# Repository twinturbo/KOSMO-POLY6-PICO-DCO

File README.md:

# KOSMO-POLY6-PICO-DCO 
This repository contains KICAD Schematics, PCB and front panel to build a 6 voice Raspberry Pi Pico Based Digitaly Controlled Oscilator for the "Polykit" Inspired 6 Channel Synth in Kosmo Format [Look Mum No Computer LMNK]. The credit for the desigin and code goes to the original Project by Jan Knipper AKA PolyKit [PolyKit DCO](https://github.com/polykit/pico-dco)

This project requires a Raspbery Pi Pico MCU.

Parts of the following information are by Jan AKA Polykit from the original repository

## About KOSMO-POLY6
The [POLY6](https://github.com/twinturbo/KOSMO-POLY6) GIT contains the details of the porject as a whole, this is one module.

Other modules in the line up are

- KOSMO-POLY6-PICO-DCO - Complete [ DCO ](https://github.com/twinturbo/KOSMO-POLY6-PICO-DCO)
- KOSMO-POLY6-DRUID-DCO -(TBD).
- KOSMO-POLY6-JACKS - Complete. [ JACKS ](https://github.com/twinturbo/KOSMO-POLY6-JACKS)
- KOSMO-POLY6-MIX - In design.
- KOSMO-POLY6-ADSR - In Production with JLCPCB.
- KOSMO-POLY6-VCA - In design.
- KOSMO-POLY6-CONTROLS - (TBD).
- KOSMO-POLY6 Filter - (TBD).
- KOSMO-POLY6-PG Programmer - (TBD)
- KOSMO-POLY6-MetricST-Front-Panel - (TBD)

# KOSMO-POLY6-PICO-DCO Details

The DCO utilises a Raspbery PI Pico using it's PWM Pins to generate a highly accurate frequency and gate signals. It can be controlled by USB MIDI or Standard 5 Pin serial MIDI. The analog oscillator part is based on the Juno 106 and generates sawtooth and square wave signal with a 10Vpp amplitude. Amplitude compensation is done by a smoothed PWM signal coming from the Pico.

## Key features

- Digitally controlled analog oscillator using a Raspberry Pi Pico
- Up to six voices
- Voice stacking             ------ [ requires sub control board ] See > Not Done
- Detuning of voices         ------ [ requires sub control board ] See > Not Done
- Frequency modulation (FM)  ------ [ requires sub control board ] See > Not Done
- Separate gate signal 
- DIN MIDI serial input
- USB MIDI input
- MIDI pitch bend (Via MIDI CC )
- Portamento with adjustable speed ( Via MIDI CC )
- Voltage and Midi telltale LED's
- Power pass through for sub modules.

## How does Jan's Sound & Look
These are examples of how the originator Jan Knipper's sound.
This is how it sounds: 

- [Ramp sample](https://soundcloud.com/polykit/pico-dco-ramp) 
- [Pulse sample](https://soundcloud.com/polykit/pico-dco-pulse) 
- [Polyphonic sample](https://soundcloud.com/polykit/pico-dco-polyphonic)

And in use with Jan 
- Youtube[Tube](https://www.youtube.com/watch?v=vj-DSh6yfM0)
- Youtube[Tube](https://www.youtube.com/watch?v=go1mErOdtsU)

## Schematics and PCB
Schematics in Kicad format can be found for the PCB and Front Panel

[MAIN-BOARD](HARDWARE/MAIN-BOARD) 
[MAIN-BOARD](HARDWARE/FRONT_PANEL) 

Gerber files for the PCB and front panel can be found [here](HARDWARE\PCB-PRINTS).

## Pictures 

## Installation on the paspbery Pi Pico (simple)
The software has been written in C++ and compiled into a uf2 format for the PICO, 

Two files are provided in the software/build folder along with the source code in the software folder

### Disabled Options
pico-dco-optdisab.uf2 is built with the options for FM, STACK and Detune disabled. This is ideal if you don't have these inputs connected.

//#define USE_ADC_STACK_VOICES // gpio 28 (adc 2)

//#define USE_ADC_DETUNE       // gpio 27 (adc 1)

//#define USE_ADC_FM           // gpio 26 (adc 0)

### Enabled Options
pico-dco-options.uf2 has the above options enabled.

#define USE_ADC_STACK_VOICES // gpio 28 (adc 2)

#define USE_ADC_DETUNE       // gpio 27 (adc 1)

#define USE_ADC_FM           // gpio 26 (adc 0)

### Writing to the MCU.

You will need the file on your computer, and whilst plugging in the PICO to USB hold the `BOOTSEL` button. 

The computer should recognise it as a Mass storage device, Copy desired UF2 file  onto the USB mass storage device. The PICO will reboot into operating mode. Note that if you run the bootsel again the file will not be there, it's not possible to confirm the upload.

## Usage

After building the module and installing the Pico should register as USB MIDI device. Alternatively serial MIDI input is available. The DCO listens to note on/note off messages on MIDI channel 1. Pitch bend is also supported. Portamento can be enabled by MIDI CC message #65, portamento time can be adjusted by CC message #5.

MIDI Device in Cakewalk

The 6 notes play all the time, hence there is a need for an ADSR and VCA to close the note off. Each new note played replaces the oldest in the group in a cyclic fashion.

## Detuning, stacking and FM

The built-in analog-to-digital converter can be used to modulate these parameters. You can add an external control voltage (0-3.3V) to that input pins. These features can be disabled by commenting (`//`) the following lines:

As mentioned above, these are not implemented in hardware on this module but a seperate control module needs to be built. 

#define USE_ADC_STACK_VOICES // gpio 28 (adc 2)

#define USE_ADC_DETUNE       // gpio 27 (adc 1)

#define USE_ADC_FM           // gpio 26 (adc 0)

Hardware wise the FM needs to be biased at 1.675v for zero input , the notes on this can be found in the source code **loop void adc_task()**

## Quirks

Initialy the voices will be floating on startup, which if directly outputed ( not through an ADSR/VCA ) may present as noise, as each of the voices is initialised by a key press the noise will go away. 

## Changes 
TwinTurbo 12/3/23 - 
Ref: > https://lookmumnocomputer.discourse.group/t/raspberry-pi-pico-dco/3421/90
updated source code from 0x90 to 0x9F

# References
The Original 
https://github.com/polykit/pico-dco

https://blog.thea.codes/the-design-of-the-juno-dco/

https://electricdruid.net/roland-juno-dcos/

https://www.youtube.com/watch?v=yYnQYF_Xa8g

https://github.com/raspberrypi/pico-examples/tree/master/pio/pwm

https://github.com/raspberrypi/pico-examples/tree/master/pio/pio_blink

https://github.com/raspberrypi/pico-examples/tree/master/pwm/hello_pwm

https://qiita.com/jamjam/items/f2fdd5c072ff348fd809

https://github.com/infovore/pico-example-midi

https://learn.sparkfun.com/tutorials/midi-tutorial/all

http://www.music-software-development.com/midi-tutorial.html

http://midi.teragonaudio.com/tech/midispec/run.htm

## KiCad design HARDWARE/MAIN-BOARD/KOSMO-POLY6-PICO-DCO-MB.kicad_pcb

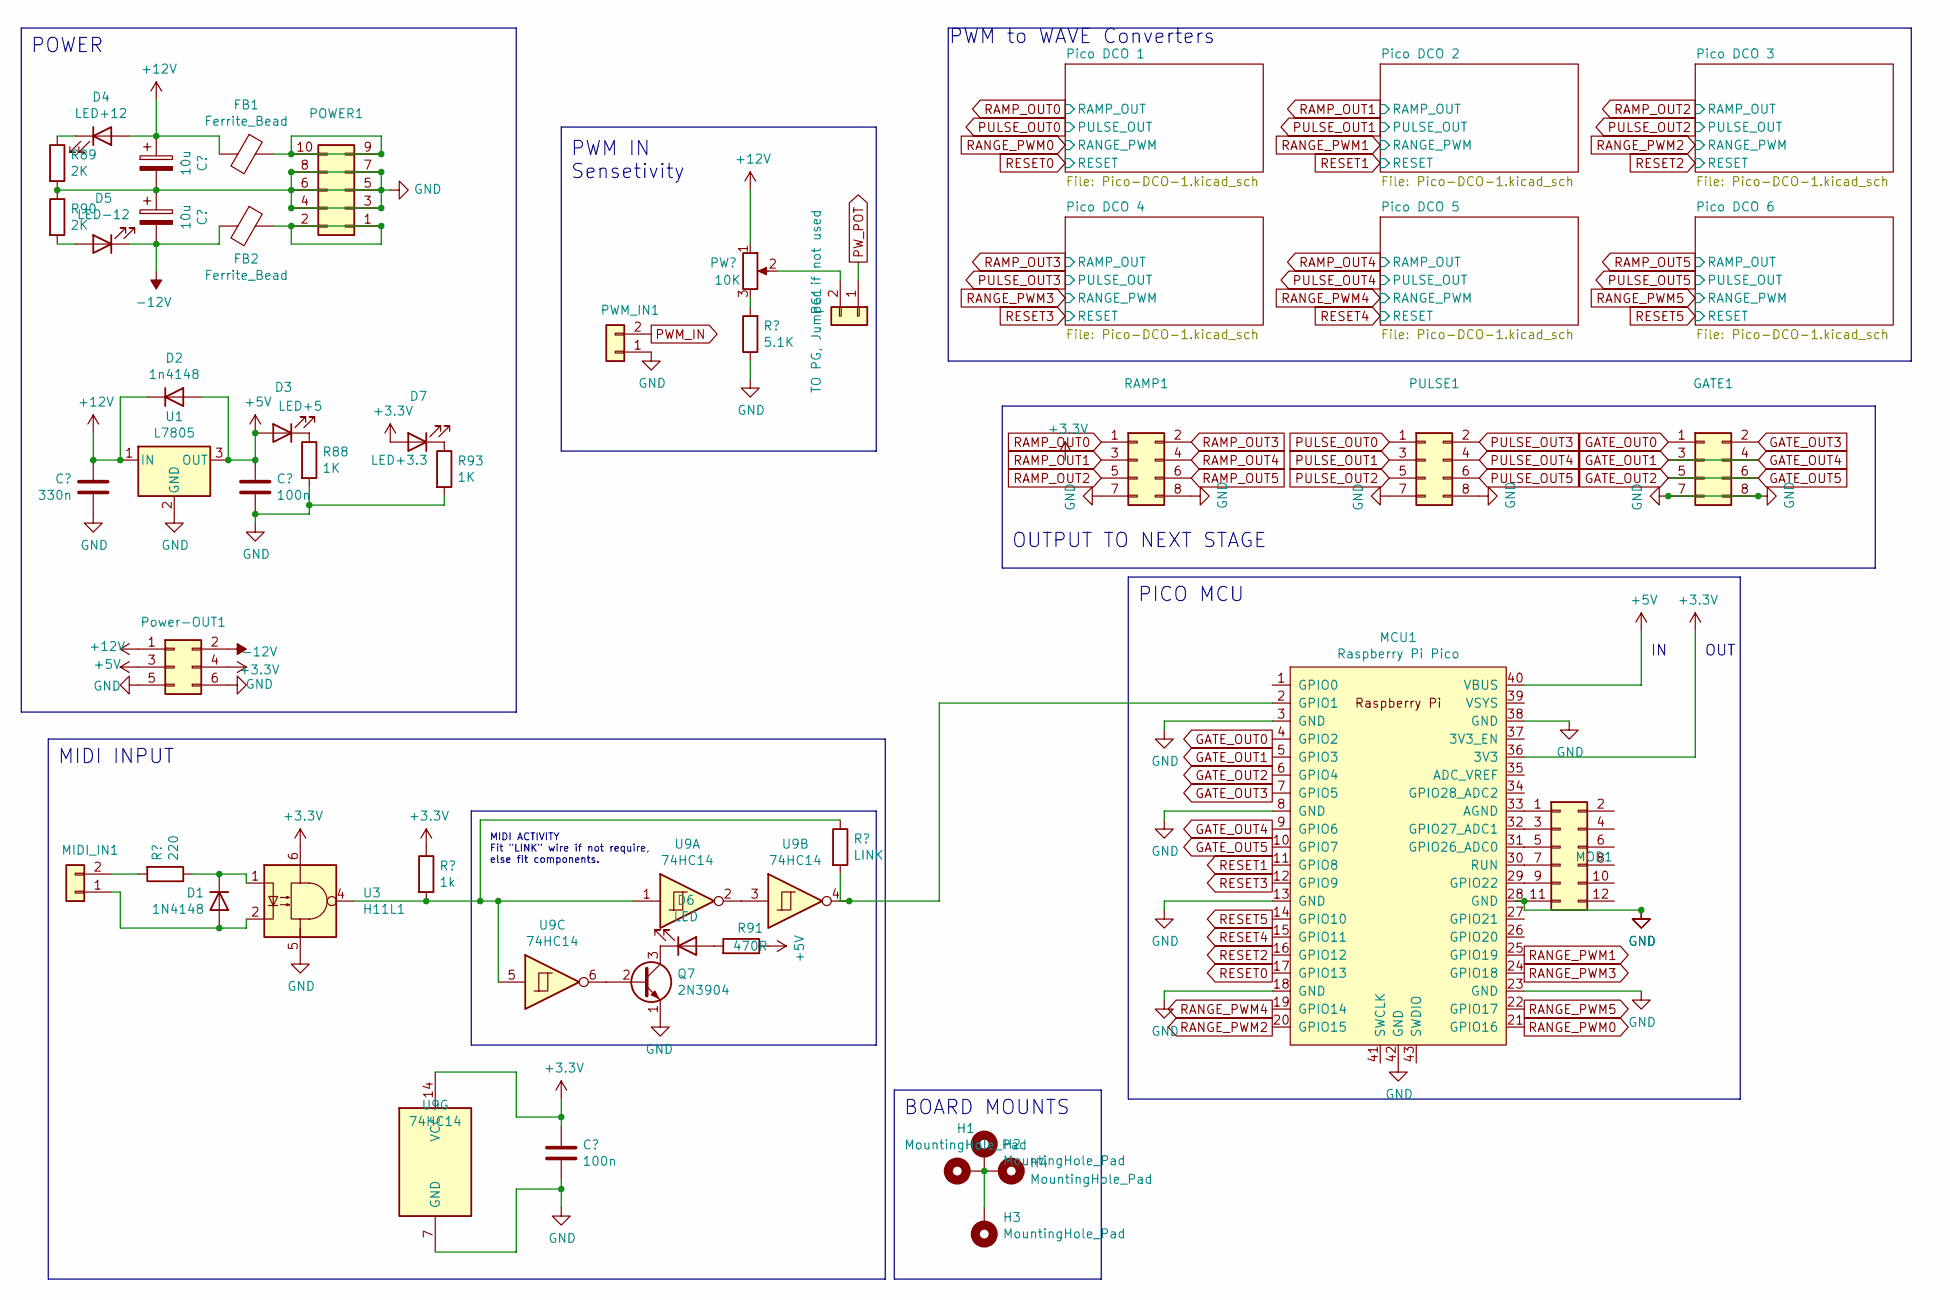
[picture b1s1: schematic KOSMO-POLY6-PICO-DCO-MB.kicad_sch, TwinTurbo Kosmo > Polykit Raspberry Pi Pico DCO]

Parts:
C6: 330n; C_Rect_L7.2mm_W4.5mm_P5.00mm_FKS2_FKP2_MKS2_MKP2
C7, C10: 100n; C_Rect_L7.2mm_W4.5mm_P5.00mm_FKS2_FKP2_MKS2_MKP2
C8, C9: 10u; CP_Radial_D5.0mm_P2.00mm
D1: 1N4148; D_DO-35_SOD27_P7.62mm_Horizontal
D2: 1n4148; D_DO-35_SOD27_P7.62mm_Horizontal
D3: LED+5; LED_D5.0mm
D4: LED+12; LED_D5.0mm
D5: LED-12; LED_D5.0mm
D6: LED; LED_D5.0mm
D7: LED+3.3; LED_D5.0mm
FB1, FB2: Ferrite_Bead; R_Axial_DIN0207_L6.3mm_D2.5mm_P10.16mm_Horizontal
GATE1: Conn_02x04_Odd_Even; IDC-Header_2x04_P2.54mm_Vertical
H1, H2, H3, H4: MountingHole_Pad; MountingHole_3.2mm_M3_DIN965_Pad
MCU1: Raspberry Pi Pico; RPi_Pico_SMD_TH
MIDI_IN1: Conn_01x02; Molex_KK-254_AE-6410-02A_1x02_P2.54mm_Vertical
MOD1: Conn_01x10; IDC-Header_2x06_P2.54mm_Vertical
PG1: TO PG, Jumper if not used; Molex_KK-254_AE-6410-02A_1x02_P2.54mm_Vertical
POWER1: Conn_02x05_Odd_Even; IDC-Header_2x05_P2.54mm_Vertical
PULSE1: Conn_02x04_Odd_Even; IDC-Header_2x04_P2.54mm_Vertical
PWM_IN1: Conn_01x02; Molex_KK-254_AE-6410-02A_1x02_P2.54mm_Vertical
PW_POT1: 10K; Potentiometer_Alps_RK09K_Single_Vertical
Power-OUT1: Conn_02x04_Odd_Even; IDC-Header_2x03_P2.54mm_Vertical
Q7: 2N3904; TO-92_Inline
R4: 5.1K; R_Axial_DIN0207_L6.3mm_D2.5mm_P2.54mm_Vertical
R16: 220; R_Axial_DIN0207_L6.3mm_D2.5mm_P2.54mm_Vertical
R17: 1k; R_Axial_DIN0207_L6.3mm_D2.5mm_P2.54mm_Vertical
R88, R93: 1K; R_Axial_DIN0207_L6.3mm_D2.5mm_P2.54mm_Vertical
R89, R90: 2K; R_Axial_DIN0207_L6.3mm_D2.5mm_P2.54mm_Vertical
R91: 470R; R_Axial_DIN0207_L6.3mm_D2.5mm_P2.54mm_Vertical
R92: LINK; R_Axial_DIN0207_L6.3mm_D2.5mm_P2.54mm_Vertical
RAMP1: Conn_02x04_Odd_Even; IDC-Header_2x04_P2.54mm_Vertical
U1: L7805; TO-220-3_Vertical
U3: H11L1; DIP-6_W7.62mm_Socket_LongPads
U9: 74HC14; DIP-14_W7.62mm

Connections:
+3V3: C10.1, D7.2 (A), MCU1.36 (3V3), Power-OUT1.4, R17.1, U3.6, U9.14 (VCC)
+5V: C7.1, D2.2 (A), D3.2 (A), MCU1.40 (VBUS), Power-OUT1.3, R91.1, U1.3 (OUT)
+12V: C6.2, C8.1, D2.1 (K), D4.2 (A), FB1.2, PW_POT1.1, Power-OUT1.1, U1.1 (IN); also elsewhere on the board
-12V: C9.2, D5.1 (K), FB2.2, Power-OUT1.2; also elsewhere on the board
GATE_OUT0: GATE1.1, MCU1.4 (GPIO2)
GATE_OUT1: GATE1.3, GATE1.4, MCU1.5 (GPIO3), MCU1.9 (GPIO6)
GATE_OUT2: GATE1.5, GATE1.6, MCU1.6 (GPIO4), MCU1.10 (GPIO7)
GATE_OUT3: GATE1.2, MCU1.7 (GPIO5)
GND: C6.1, C7.2, C8.2, C9.1, C10.2, GATE1.7, GATE1.8, MCU1.3 (GND), MCU1.8 (GND), MCU1.13 (GND), MCU1.18 (GND), MCU1.23 (GND), MCU1.28 (GND), MCU1.38 (GND), MCU1.42 (GND), MOD1.11, POWER1.3, POWER1.4, POWER1.5, POWER1.6, POWER1.7, POWER1.8, PULSE1.7, PULSE1.8, PWM_IN1.1, Power-OUT1.5, Power-OUT1.6, Q7.1 (E), R4.1, R88.2, R89.2, R90.1, R93.2, RAMP1.7, RAMP1.8, U1.2 (GND), U3.5, U9.7 (GND); also elsewhere on the board
unnamed: D1.1 (K), R16.1, U3.1
unnamed: D1.2 (A), MIDI_IN1.1, U3.2
unnamed: D3.1 (K), R88.1
unnamed: D4.1 (K), R89.1
unnamed: D5.2 (A), R90.2
unnamed: D6.1 (K), Q7.3 (C)
unnamed: D6.2 (A), R91.2
unnamed: D7.1 (K), R93.1
unnamed: FB1.1, POWER1.9, POWER1.10
unnamed: FB2.1, POWER1.1, POWER1.2
unnamed: H1.1, H2.1, H3.1, H4.1
unnamed: MCU1.2 (GPIO1), R92.2, U9.4
unnamed: MCU1.29 (GPIO22), MOD1.9
unnamed: MCU1.30 (RUN), MOD1.7
unnamed: MCU1.31 (GPIO26_ADC0), MOD1.5
unnamed: MCU1.32 (GPIO27_ADC1), MOD1.3
unnamed: MCU1.33 (AGND), MOD1.1
unnamed: MIDI_IN1.2, R16.2
unnamed: PG1.2, PW_POT1.2
unnamed: PW_POT1.3, R4.2
unnamed: Q7.2 (B), U9.6
unnamed: R17.2, R92.1, U3.4, U9.1, U9.5
unnamed: U9.2, U9.3
PULSE_OUT0: PULSE1.1; also elsewhere on the board
PULSE_OUT1: PULSE1.3; also elsewhere on the board
PULSE_OUT2: PULSE1.5; also elsewhere on the board
PULSE_OUT3: PULSE1.2; also elsewhere on the board
PULSE_OUT4: PULSE1.4; also elsewhere on the board
PULSE_OUT5: PULSE1.6; also elsewhere on the board
PWM_IN: PWM_IN1.2; also elsewhere on the board
PW_POT: PG1.1; also elsewhere on the board
RAMP_OUT0: RAMP1.1; also elsewhere on the board
RAMP_OUT1: RAMP1.3; also elsewhere on the board
RAMP_OUT2: RAMP1.5; also elsewhere on the board
RAMP_OUT3: RAMP1.2; also elsewhere on the board
RAMP_OUT4: RAMP1.4; also elsewhere on the board
RAMP_OUT5: RAMP1.6; also elsewhere on the board
RANGE_PWM0: MCU1.21 (GPIO16); also elsewhere on the board
RANGE_PWM1: MCU1.25 (GPIO19); also elsewhere on the board
RANGE_PWM2: MCU1.20 (GPIO15); also elsewhere on the board
RANGE_PWM3: MCU1.24 (GPIO18); also elsewhere on the board
RANGE_PWM4: MCU1.19 (GPIO14); also elsewhere on the board
RANGE_PWM5: MCU1.22 (GPIO17); also elsewhere on the board
RESET0: MCU1.17 (GPIO13); also elsewhere on the board
RESET1: MCU1.11 (GPIO8); also elsewhere on the board
RESET2: MCU1.16 (GPIO12); also elsewhere on the board
RESET3: MCU1.12 (GPIO9); also elsewhere on the board
RESET4: MCU1.15 (GPIO11); also elsewhere on the board
RESET5: MCU1.14 (GPIO10); also elsewhere on the board

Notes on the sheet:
POWER
PICO MCU
OUT
PWM to WAVE Converters
MIDI ACTIVITY Fit "LINK" wire if not require, else fit components.
BOARD MOUNTS
PWM IN Sensetivity
MIDI INPUT
OUTPUT TO NEXT STAGE

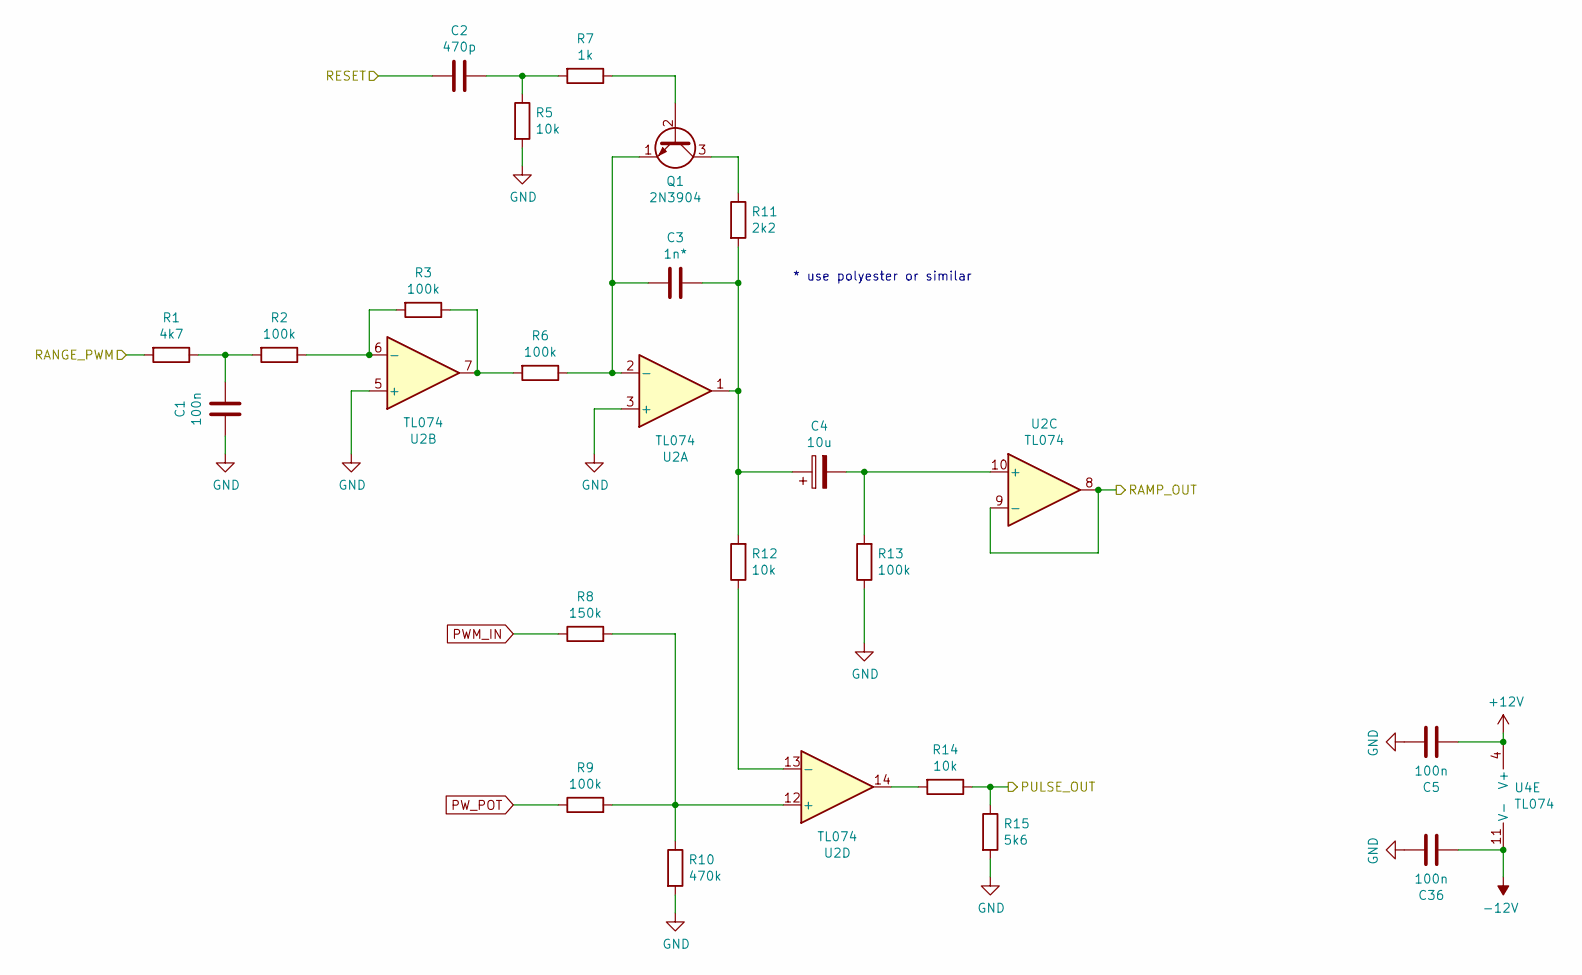
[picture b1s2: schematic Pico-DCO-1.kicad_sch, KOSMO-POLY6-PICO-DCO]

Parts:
C1, C5, C36: 100n; C_Rect_L7.2mm_W4.5mm_P5.00mm_FKS2_FKP2_MKS2_MKP2
C2: 470p; C_Rect_L7.2mm_W4.5mm_P5.00mm_FKS2_FKP2_MKS2_MKP2
C3: 1n*; C_Rect_L7.2mm_W4.5mm_P5.00mm_FKS2_FKP2_MKS2_MKP2
C4: 10u; CP_Radial_D5.0mm_P2.00mm
Q1: 2N3904; TO-92_Wide
R1: 4k7; R_Axial_DIN0207_L6.3mm_D2.5mm_P2.54mm_Vertical
R2, R3, R6, R9, R13: 100k; R_Axial_DIN0207_L6.3mm_D2.5mm_P2.54mm_Vertical
R5, R12, R14: 10k; R_Axial_DIN0207_L6.3mm_D2.5mm_P2.54mm_Vertical
R7: 1k; R_Axial_DIN0207_L6.3mm_D2.5mm_P2.54mm_Vertical
R8: 150k; R_Axial_DIN0207_L6.3mm_D2.5mm_P2.54mm_Vertical
R10: 470k; R_Axial_DIN0207_L6.3mm_D2.5mm_P2.54mm_Vertical
R11: 2k2; R_Axial_DIN0207_L6.3mm_D2.5mm_P2.54mm_Vertical
R15: 5k6; R_Axial_DIN0207_L6.3mm_D2.5mm_P2.54mm_Vertical
U2, U4: TL074; DIP-14_W7.62mm_Socket_LongPads

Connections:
+12V: C5.2, U2.4 (V+), U4.4 (V+); also elsewhere on the board
-12V: C36.2, U2.11 (V-), U4.11 (V-); also elsewhere on the board
GND: C1.2, C5.1, C36.1, R5.2, R10.2, R13.1, R15.2, U2.3 (+), U2.5 (+), U4.3 (+), U4.5 (+); also elsewhere on the board
unnamed: C1.1, R1.1, R2.2
unnamed: C2.1, R5.1, R7.2
unnamed: C3.1, C4.1, R11.2, R12.2, U2.1
unnamed: C3.2, Q1.1 (E), R6.1, U2.2 (-)
unnamed: C4.2, R13.2, U2.10 (+)
unnamed 16: U4.1; also elsewhere on the board
unnamed 17: U4.2 (-); also elsewhere on the board
unnamed 18: U4.10 (+); also elsewhere on the board
unnamed: Q1.2 (B), R7.1
unnamed: Q1.3 (C), R11.1
unnamed: R2.1, R3.2, U2.6 (-)
unnamed: R3.1, R6.2, U2.7
unnamed: R8.2, R9.2, R10.1, U2.12 (+)
unnamed: R12.1, U2.13 (-)
unnamed: R14.2, U2.14
unnamed 93: U4.6 (-); also elsewhere on the board
unnamed 94: U4.7; also elsewhere on the board
unnamed 95: U4.12 (+); also elsewhere on the board
unnamed 96: U4.13 (-); also elsewhere on the board
unnamed 97: U4.14; also elsewhere on the board
PULSE_OUT0: R14.1, R15.1; also elsewhere on the board
PWM_IN: R8.1; also elsewhere on the board
PW_POT: R9.1; also elsewhere on the board
RAMP_OUT0: U2.8, U2.9 (-); also elsewhere on the board
RAMP_OUT1: U4.8, U4.9 (-); also elsewhere on the board
RANGE_PWM0: R1.2; also elsewhere on the board
RESET0: C2.2; also elsewhere on the board

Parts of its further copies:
C11, C15, C16, C20, C21, C25, C26, C30, C31, C35, C37, C38, C39, C40, C41: 100n; C_Rect_L7.2mm_W4.5mm_P5.00mm_FKS2_FKP2_MKS2_MKP2
C12, C17, C22, C27, C32: 470p; C_Rect_L7.2mm_W4.5mm_P5.00mm_FKS2_FKP2_MKS2_MKP2
C13, C18, C23, C28, C33: 1n*; C_Rect_L7.2mm_W4.5mm_P5.00mm_FKS2_FKP2_MKS2_MKP2
C14, C19, C24, C29, C34: 10u; CP_Radial_D5.0mm_P2.00mm
Q2, Q3, Q4, Q5, Q6: 2N3904; TO-92_Wide
R18, R32, R46, R60, R74: 4k7; R_Axial_DIN0207_L6.3mm_D2.5mm_P2.54mm_Vertical
R19, R20, R22, R25, R29, R33, R34, R36, R39, R43, R47, R48, R50, R53, R57, R61, R62, R64, R67, R71, R75, R76, R78, R81, R85: 100k; R_Axial_DIN0207_L6.3mm_D2.5mm_P2.54mm_Vertical
R21, R28, R30, R35, R42, R44, R49, R56, R58, R63, R70, R72, R77, R84, R86: 10k; R_Axial_DIN0207_L6.3mm_D2.5mm_P2.54mm_Vertical
R23, R37, R51, R65, R79: 1k; R_Axial_DIN0207_L6.3mm_D2.5mm_P2.54mm_Vertical
R24, R38, R52, R66, R80: 150k; R_Axial_DIN0207_L6.3mm_D2.5mm_P2.54mm_Vertical
R26, R40, R54, R68, R82: 470k; R_Axial_DIN0207_L6.3mm_D2.5mm_P2.54mm_Vertical
R27, R41, R55, R69, R83: 2k2; R_Axial_DIN0207_L6.3mm_D2.5mm_P2.54mm_Vertical
R31, R45, R59, R73, R87: 5k6; R_Axial_DIN0207_L6.3mm_D2.5mm_P2.54mm_Vertical
U5, U6, U7, U8: TL074; DIP-14_W7.62mm_Socket_LongPads

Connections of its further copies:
+12V: C15.2, C20.2, C25.2, C30.2, C35.2, U5.4 (V+), U6.4 (V+), U7.4 (V+), U8.4 (V+); also elsewhere on the board
-12V: C37.2, C38.2, C39.2, C40.2, C41.2, U5.11 (V-), U6.11 (V-), U7.11 (V-), U8.11 (V-); also elsewhere on the board
GND: C11.2, C15.1, C16.2, C20.1, C21.2, C25.1, C26.2, C30.1, C31.2, C35.1, C37.1, C38.1, C39.1, C40.1, C41.1, R21.2, R26.2, R29.1, R31.2, R35.2, R40.2, R43.1, R45.2, R49.2, R54.2, R57.1, R59.2, R63.2, R68.2, R71.1, R73.2, R77.2, R82.2, R85.1, R87.2, U5.3 (+), U5.5 (+), U6.3 (+), U6.5 (+), U7.3 (+), U7.5 (+), U8.3 (+), U8.5 (+); also elsewhere on the board
unnamed: C11.1, R18.1, R19.2
unnamed: C12.1, R21.1, R23.2
unnamed 16: C13.1, C14.1, R27.2, R28.2; also elsewhere on the board
unnamed 17: C13.2, Q2.1 (E), R22.1; also elsewhere on the board
unnamed 18: C14.2, R29.2; also elsewhere on the board
unnamed: C16.1, R32.1, R33.2
unnamed: C17.1, R35.1, R37.2
unnamed: C18.1, C19.1, R41.2, R42.2, U5.1
unnamed: C18.2, Q3.1 (E), R36.1, U5.2 (-)
unnamed: C19.2, R43.2, U5.10 (+)
unnamed: C21.1, R46.1, R47.2
unnamed: C22.1, R49.1, R51.2
unnamed: C23.1, C24.1, R55.2, R56.2, U6.1
unnamed: C23.2, Q4.1 (E), R50.1, U6.2 (-)
unnamed: C24.2, R57.2, U6.10 (+)
unnamed: C26.1, R60.1, R61.2
unnamed: C27.1, R63.1, R65.2
unnamed: C28.1, C29.1, R69.2, R70.2, U7.1
unnamed: C28.2, Q5.1 (E), R64.1, U7.2 (-)
unnamed: C29.2, R71.2, U7.10 (+)
unnamed: C31.1, R74.1, R75.2
unnamed: C32.1, R77.1, R79.2
unnamed: C33.1, C34.1, R83.2, R84.2, U8.1
unnamed: C33.2, Q6.1 (E), R78.1, U8.2 (-)
unnamed: C34.2, R85.2, U8.10 (+)
unnamed: Q2.2 (B), R23.1
unnamed: Q2.3 (C), R27.1
unnamed: Q3.2 (B), R37.1
unnamed: Q3.3 (C), R41.1
unnamed: Q4.2 (B), R51.1
unnamed: Q4.3 (C), R55.1
unnamed: Q5.2 (B), R65.1
unnamed: Q5.3 (C), R69.1
unnamed: Q6.2 (B), R79.1
unnamed: Q6.3 (C), R83.1
unnamed 93: R19.1, R20.2; also elsewhere on the board
unnamed 94: R20.1, R22.2; also elsewhere on the board
unnamed 95: R24.2, R25.2, R26.1; also elsewhere on the board
unnamed 96: R28.1; also elsewhere on the board
unnamed 97: R30.2; also elsewhere on the board
unnamed: R33.1, R34.2, U5.6 (-)
unnamed: R34.1, R36.2, U5.7
unnamed: R38.2, R39.2, R40.1, U5.12 (+)
unnamed: R42.1, U5.13 (-)
unnamed: R44.2, U5.14
unnamed: R47.1, R48.2, U6.6 (-)
unnamed: R48.1, R50.2, U6.7
unnamed: R52.2, R53.2, R54.1, U6.12 (+)
unnamed: R56.1, U6.13 (-)
unnamed: R58.2, U6.14
unnamed: R61.1, R62.2, U7.6 (-)
unnamed: R62.1, R64.2, U7.7
unnamed: R66.2, R67.2, R68.1, U7.12 (+)
unnamed: R70.1, U7.13 (-)
unnamed: R72.2, U7.14
unnamed: R75.1, R76.2, U8.6 (-)
unnamed: R76.1, R78.2, U8.7
unnamed: R80.2, R81.2, R82.1, U8.12 (+)
unnamed: R84.1, U8.13 (-)
unnamed: R86.2, U8.14
PULSE_OUT1: R30.1, R31.1; also elsewhere on the board
PULSE_OUT2: R44.1, R45.1; also elsewhere on the board
PULSE_OUT3: R58.1, R59.1; also elsewhere on the board
PULSE_OUT4: R72.1, R73.1; also elsewhere on the board
PULSE_OUT5: R86.1, R87.1; also elsewhere on the board
PWM_IN: R24.1, R38.1, R52.1, R66.1, R80.1; also elsewhere on the board
PW_POT: R25.1, R39.1, R53.1, R67.1, R81.1; also elsewhere on the board
RAMP_OUT2: U5.8, U5.9 (-); also elsewhere on the board
RAMP_OUT3: U6.8, U6.9 (-); also elsewhere on the board
RAMP_OUT4: U7.8, U7.9 (-); also elsewhere on the board
RAMP_OUT5: U8.8, U8.9 (-); also elsewhere on the board
RANGE_PWM1: R18.2; also elsewhere on the board
RANGE_PWM2: R32.2; also elsewhere on the board
RANGE_PWM3: R46.2; also elsewhere on the board
RANGE_PWM4: R60.2; also elsewhere on the board
RANGE_PWM5: R74.2; also elsewhere on the board
RESET1: C12.2; also elsewhere on the board
RESET2: C17.2; also elsewhere on the board
RESET3: C22.2; also elsewhere on the board
RESET4: C27.2; also elsewhere on the board
RESET5: C32.2; also elsewhere on the board

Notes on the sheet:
* use polyester or similar

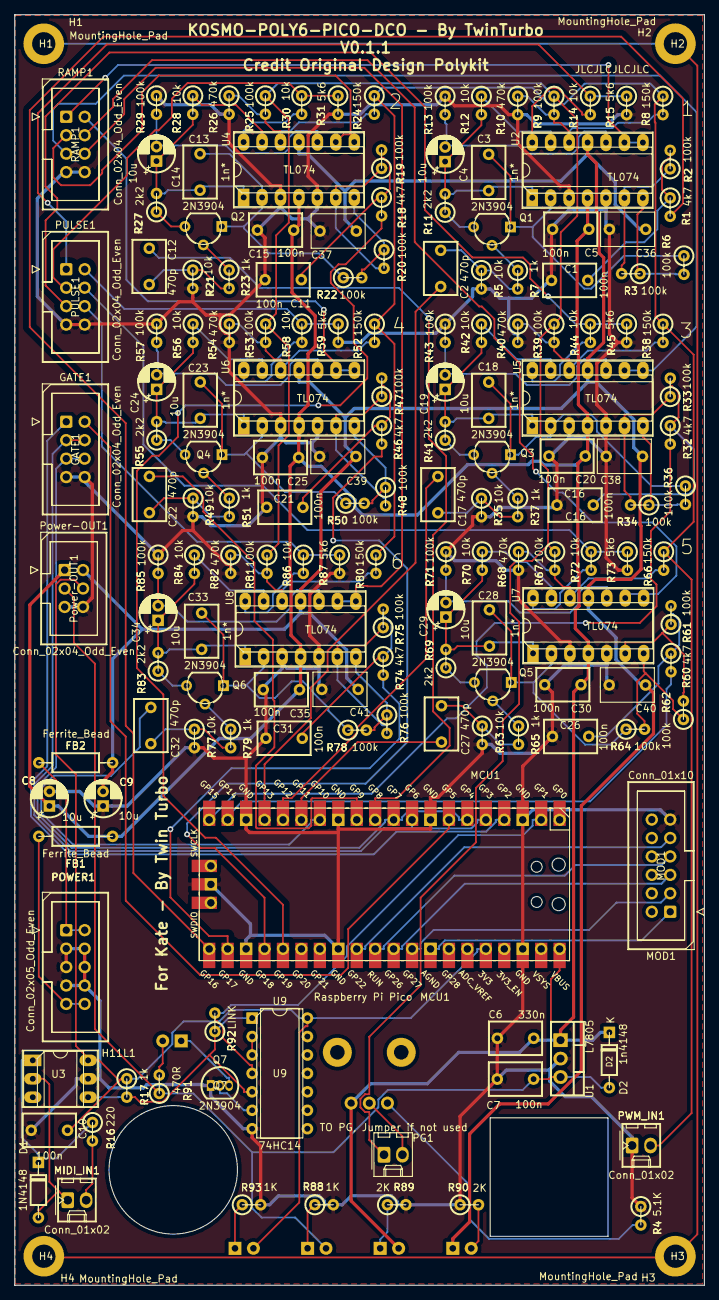
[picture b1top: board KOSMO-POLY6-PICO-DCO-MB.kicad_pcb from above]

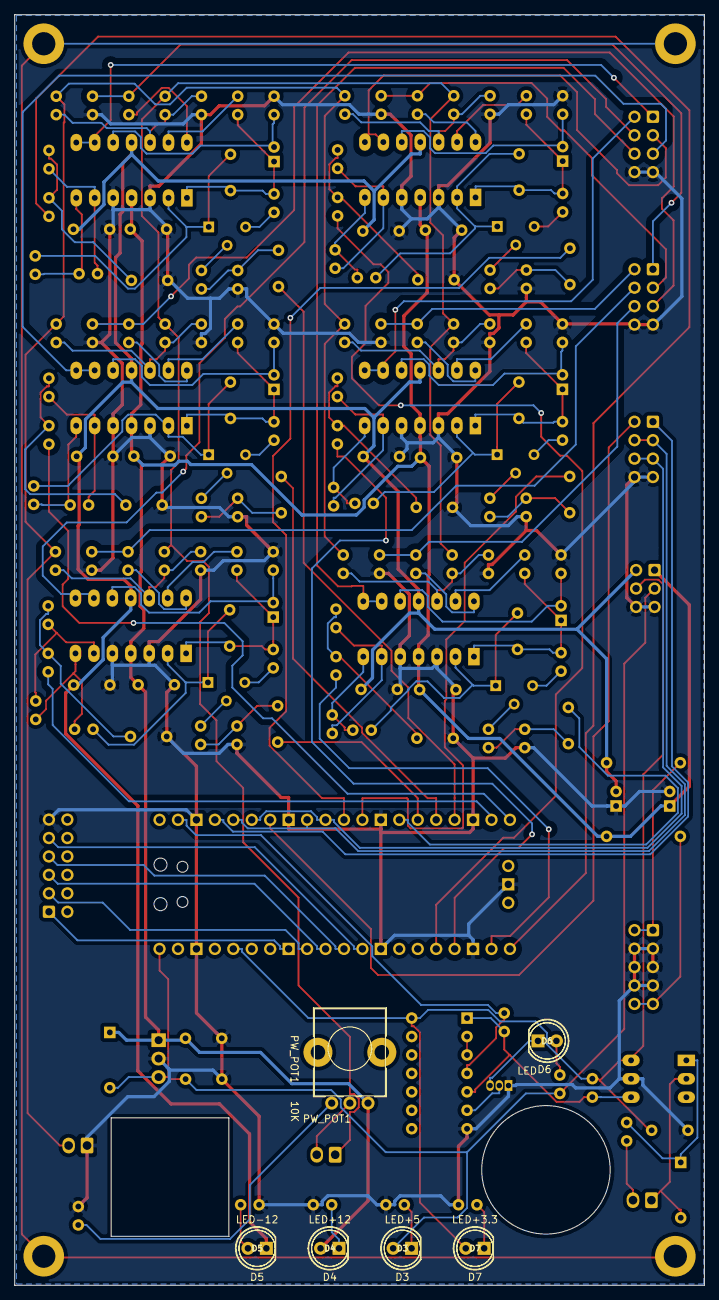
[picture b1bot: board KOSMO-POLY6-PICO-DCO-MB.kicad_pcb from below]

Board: 2 copper layers, 94.9 x 174.9 mm, 174 parts (6 on the bottom side), 130 nets.

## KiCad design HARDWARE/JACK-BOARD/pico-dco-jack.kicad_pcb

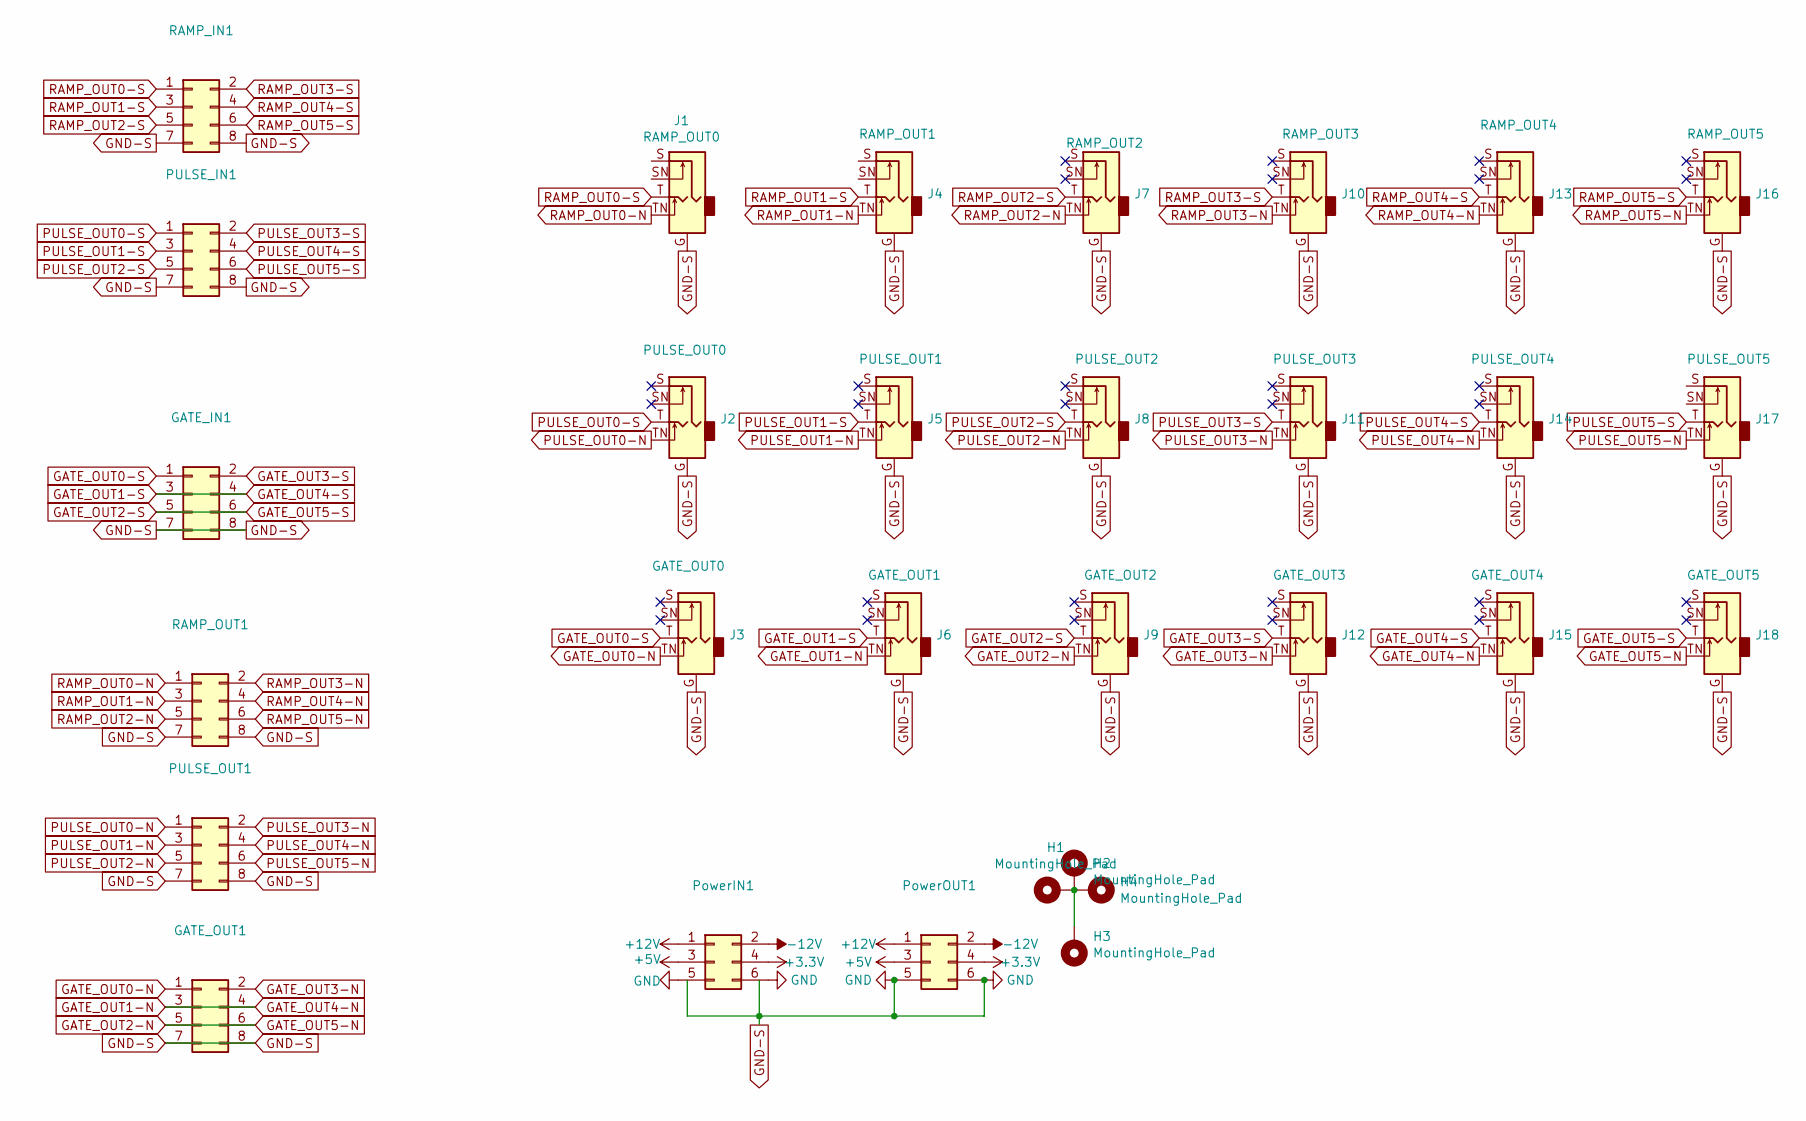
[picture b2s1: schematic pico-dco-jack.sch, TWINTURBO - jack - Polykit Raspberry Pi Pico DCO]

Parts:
GATE_IN1: Conn_02x04_Odd_Even; IDC-Header_2x04_P2.54mm_Vertical
GATE_OUT1: Conn_02x04_Odd_Even; IDC-Header_2x04_P2.54mm_Vertical
H1, H2, H3, H4: MountingHole_Pad; MountingHole_3.2mm_M3_DIN965_Pad
J1: RAMP_OUT0; Jack_6.5mmLMNC
J2: PULSE_OUT0; Jack_6.5mmLMNC
J3: GATE_OUT0; Jack_6.5mmLMNC
J4: RAMP_OUT1; Jack_6.5mmLMNC
J5: PULSE_OUT1; Jack_6.5mmLMNC
J6: GATE_OUT1; Jack_6.5mmLMNC
J7: RAMP_OUT2; Jack_6.5mmLMNC
J8: PULSE_OUT2; Jack_6.5mmLMNC
J9: GATE_OUT2; Jack_6.5mmLMNC
J10: RAMP_OUT3; Jack_6.5mmLMNC
J11: PULSE_OUT3; Jack_6.5mmLMNC
J12: GATE_OUT3; Jack_6.5mmLMNC
J13: RAMP_OUT4; Jack_6.5mmLMNC
J14: PULSE_OUT4; Jack_6.5mmLMNC
J15: GATE_OUT4; Jack_6.5mmLMNC
J16: RAMP_OUT5; Jack_6.5mmLMNC
J17: PULSE_OUT5; Jack_6.5mmLMNC
J18: GATE_OUT5; Jack_6.5mmLMNC
PULSE_IN1: Conn_02x04_Odd_Even; IDC-Header_2x04_P2.54mm_Vertical
PULSE_OUT1: Conn_02x04_Odd_Even; IDC-Header_2x04_P2.54mm_Vertical
PowerIN1: Conn_02x03_Odd_Even; IDC-Header_2x03_P2.54mm_Vertical
PowerOUT1: Conn_02x03_Odd_Even; IDC-Header_2x03_P2.54mm_Vertical
RAMP_IN1: Conn_02x04_Odd_Even; IDC-Header_2x04_P2.54mm_Vertical
RAMP_OUT1: Conn_02x04_Odd_Even; IDC-Header_2x04_P2.54mm_Vertical

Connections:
+3V3: PowerIN1.4, PowerOUT1.4
+5V: PowerIN1.3, PowerOUT1.3
+12V: PowerIN1.1, PowerOUT1.1
-12V: PowerIN1.2, PowerOUT1.2
GATE_OUT0-N: GATE_OUT1.1, J3.TN
GATE_OUT0-S: GATE_IN1.1, J3.T
GATE_OUT1-N: GATE_OUT1.3, GATE_OUT1.4, J6.TN, J15.TN
GATE_OUT1-S: GATE_IN1.3, GATE_IN1.4, J6.T, J15.T
GATE_OUT2-N: GATE_OUT1.5, GATE_OUT1.6, J9.TN, J18.TN
GATE_OUT2-S: GATE_IN1.5, GATE_IN1.6, J9.T, J18.T
GATE_OUT3-N: GATE_OUT1.2, J12.TN
GATE_OUT3-S: GATE_IN1.2, J12.T
PULSE_OUT0-N: J2.TN, PULSE_OUT1.1
PULSE_OUT0-S: J2.T, PULSE_IN1.1
PULSE_OUT1-N: J5.TN, PULSE_OUT1.3
PULSE_OUT1-S: J5.T, PULSE_IN1.3
PULSE_OUT2-N: J8.TN, PULSE_OUT1.5
PULSE_OUT2-S: J8.T, PULSE_IN1.5
PULSE_OUT3-N: J11.TN, PULSE_OUT1.2
PULSE_OUT3-S: J11.T, PULSE_IN1.2
PULSE_OUT4-N: J14.TN, PULSE_OUT1.4
PULSE_OUT4-S: J14.T, PULSE_IN1.4
PULSE_OUT5-N: J17.TN, PULSE_OUT1.6
PULSE_OUT5-S: J17.T, PULSE_IN1.6
RAMP_OUT0-N: J1.TN, RAMP_OUT1.1
RAMP_OUT0-S: J1.T, RAMP_IN1.1
RAMP_OUT1-N: J4.TN, RAMP_OUT1.3
RAMP_OUT1-S: J4.T, RAMP_IN1.3
RAMP_OUT2-N: J7.TN, RAMP_OUT1.5
RAMP_OUT2-S: J7.T, RAMP_IN1.5
RAMP_OUT3-N: J10.TN, RAMP_OUT1.2
RAMP_OUT3-S: J10.T, RAMP_IN1.2
RAMP_OUT4-N: J13.TN, RAMP_OUT1.4
RAMP_OUT4-S: J13.T, RAMP_IN1.4
RAMP_OUT5-N: J16.TN, RAMP_OUT1.6
RAMP_OUT5-S: J16.T, RAMP_IN1.6

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
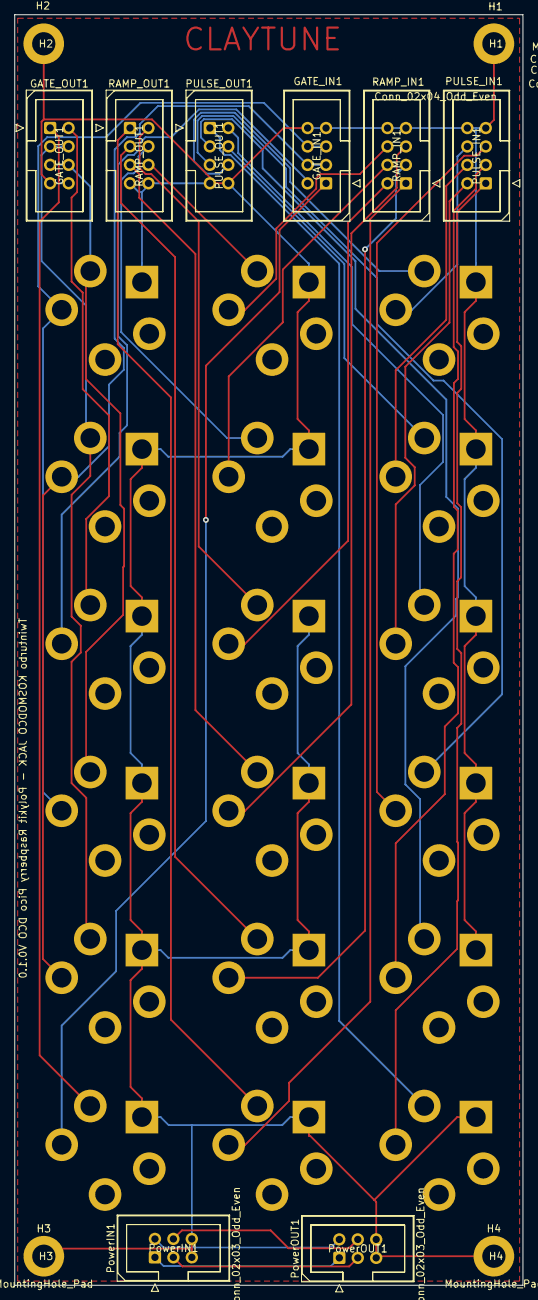
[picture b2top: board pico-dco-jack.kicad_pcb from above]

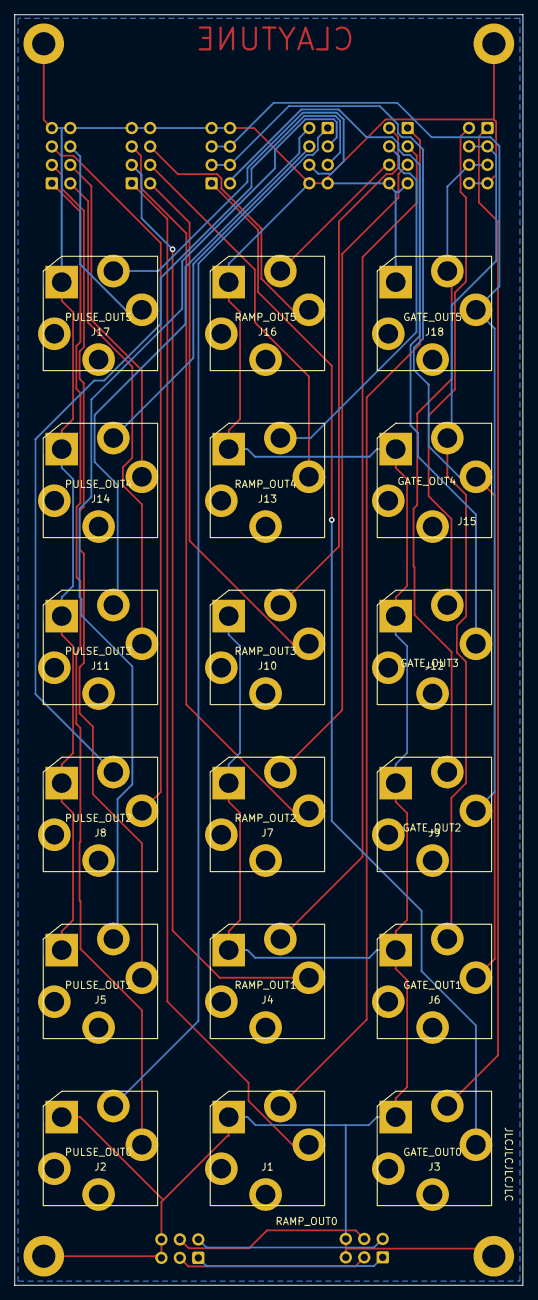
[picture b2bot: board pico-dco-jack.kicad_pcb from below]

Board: 2 copper layers, 70.0 x 175.0 mm, 30 parts (18 on the bottom side), 37 nets.

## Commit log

2023-03-06 Initialised
2023-03-06 1st Fix
2023-03-06 baord ready
2023-03-07 sync
2023-03-08 Added jumper on PWM pot to go to future PG Programmer
2023-03-08 DOCS
2023-03-12 Code Change
2023-03-12 Readme Update
2023-03-13 KICAD7 FIXLAYER
2023-05-25 holidaysync
